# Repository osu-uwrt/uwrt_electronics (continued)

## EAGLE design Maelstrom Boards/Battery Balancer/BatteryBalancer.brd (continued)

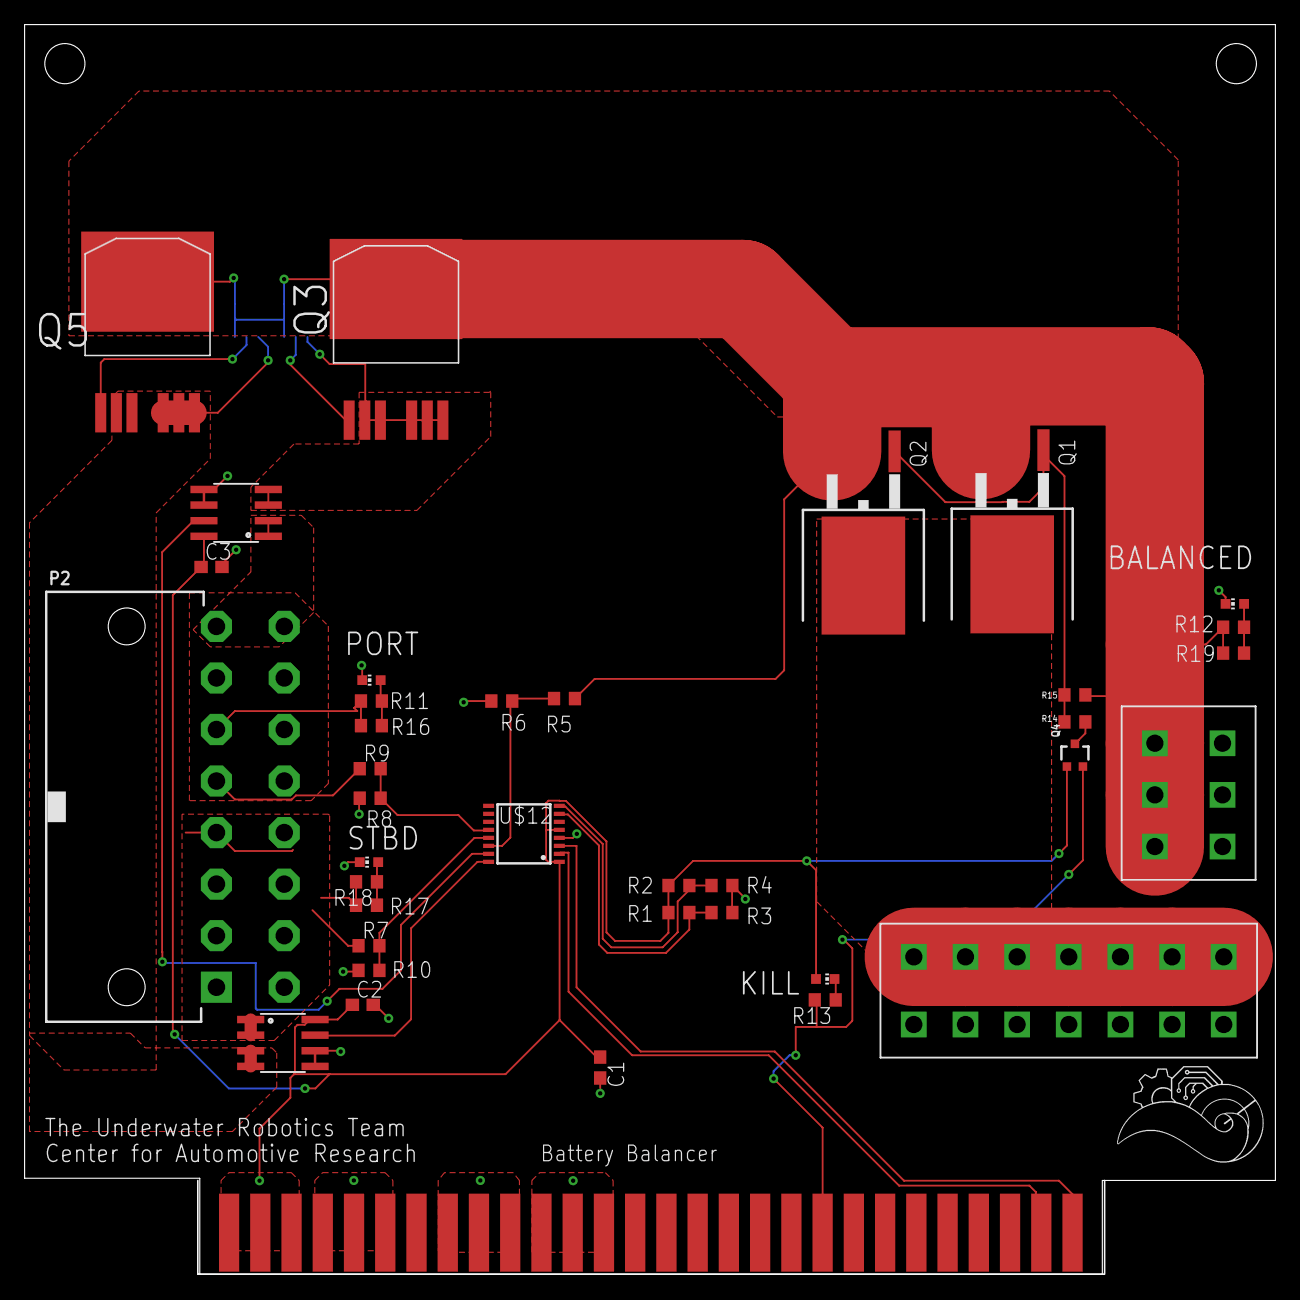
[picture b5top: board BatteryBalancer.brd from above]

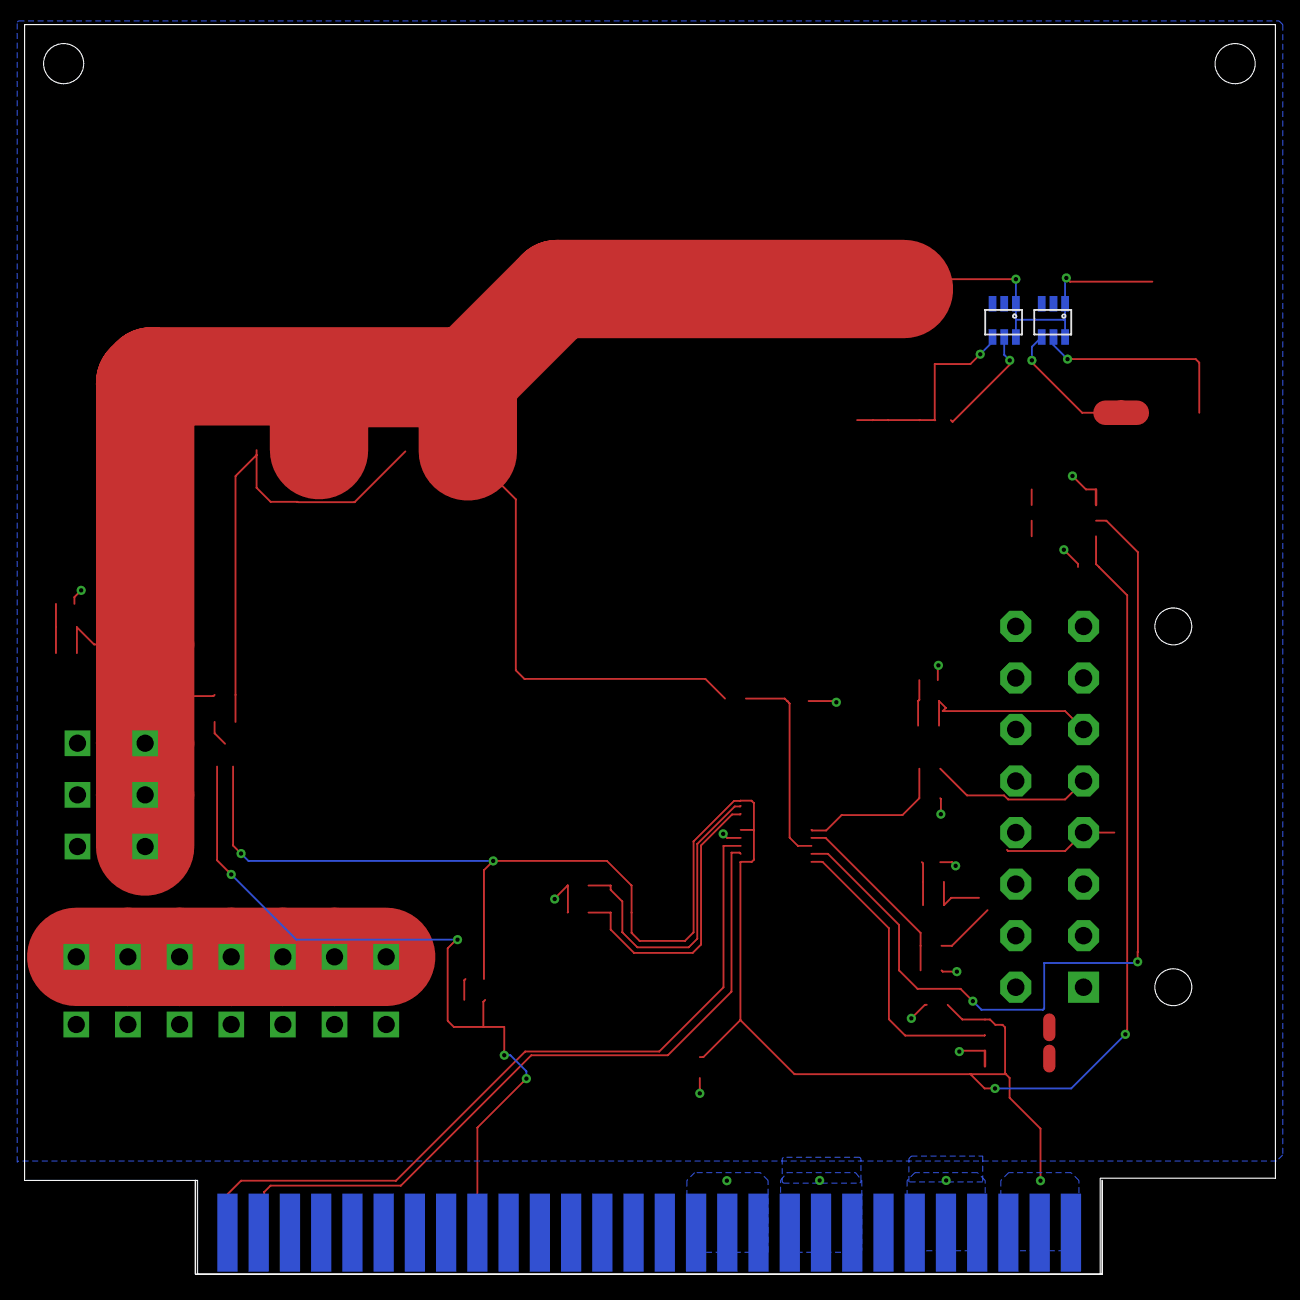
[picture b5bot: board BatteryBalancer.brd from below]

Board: 2 copper layers, 101.7 x 101.6 mm, 40 parts (2 on the bottom side), 27 nets.

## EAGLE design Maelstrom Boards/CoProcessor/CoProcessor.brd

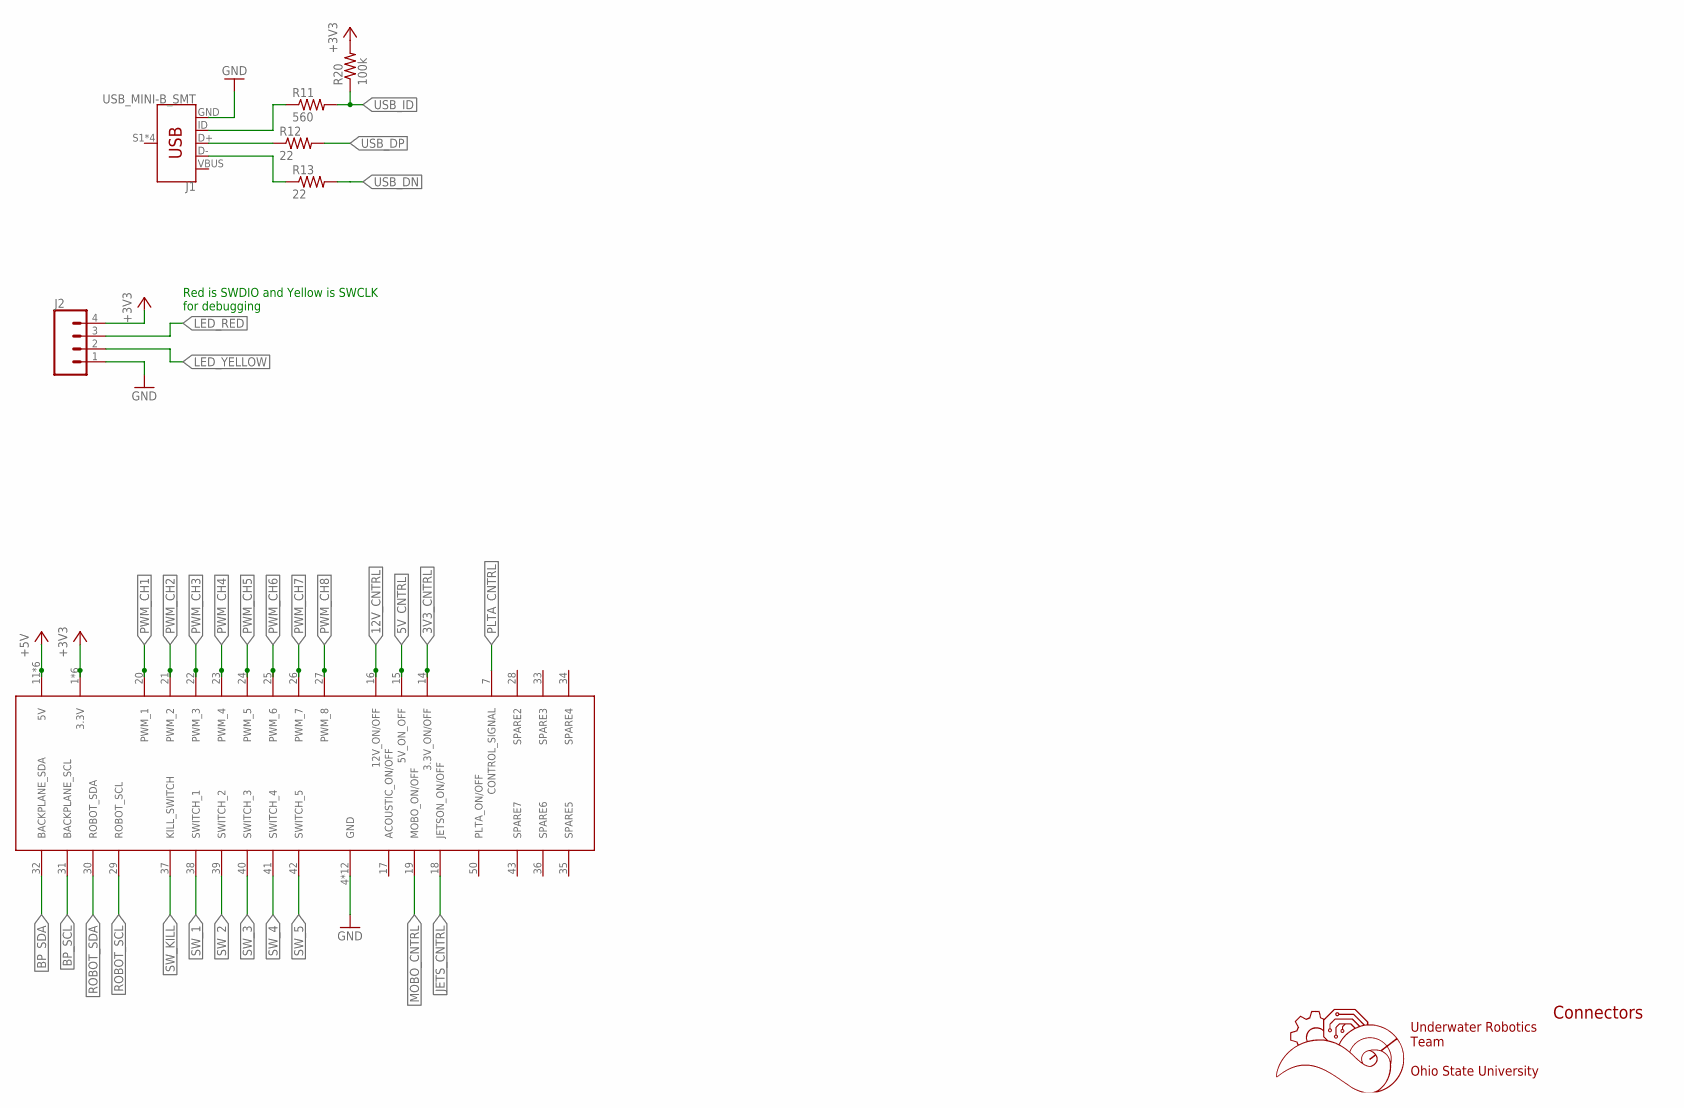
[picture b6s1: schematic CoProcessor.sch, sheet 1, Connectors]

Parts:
J1: USB_MINI-B_SMT; USB-MINIB
J2: CONN_04; 1X04
R11: 560; R0603
R12, R13: 22; R0603
R20: 100k; R0603
U$1: 5530843-EDGE; 5530843-6-BOARDFINGERS

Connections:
3V3_CNTRL: U$1.14 (3.3V_ON/OFF); also elsewhere on the board
5V_CNTRL: U$1.15 (5V_ON_OFF); also elsewhere on the board
12V_CNTRL: U$1.16 (12V_ON/OFF); also elsewhere on the board
+3V3: J2.4, R20.2, U$1.1 (3.3V), U$1.2 (3.3V), U$1.3 (3.3V), U$1.54 (3.3V), U$1.55 (3.3V), U$1.56 (3.3V); also elsewhere on the board
+5V: U$1.11 (5V), U$1.12 (5V), U$1.13 (5V), U$1.44 (5V), U$1.45 (5V), U$1.46 (5V)
BP_SCL: U$1.31 (BACKPLANE_SCL); also elsewhere on the board
BP_SDA: U$1.32 (BACKPLANE_SDA); also elsewhere on the board
GND: J1.GND, J2.1, U$1.4 (GND), U$1.5 (GND), U$1.6 (GND), U$1.8 (GND), U$1.9 (GND), U$1.10 (GND), U$1.47 (GND), U$1.48 (GND), U$1.49 (GND), U$1.51 (GND), U$1.52 (GND), U$1.53 (GND); also elsewhere on the board
JETS_CNTRL: U$1.18 (JETSON_ON/OFF); also elsewhere on the board
LED_RED: J2.3; also elsewhere on the board
LED_YELLOW: J2.2; also elsewhere on the board
MOBO_CNTRL: U$1.19 (MOBO_ON/OFF); also elsewhere on the board
unnamed: J1.ID, R11.1
unnamed: J1.D+, R12.1
unnamed: J1.D-, R13.1
PLTA_CNTRL: U$1.7 (CONTROL_SIGNAL); also elsewhere on the board
PWM_CH1: U$1.20 (PWM_1); also elsewhere on the board
PWM_CH2: U$1.21 (PWM_2); also elsewhere on the board
PWM_CH3: U$1.22 (PWM_3); also elsewhere on the board
PWM_CH4: U$1.23 (PWM_4); also elsewhere on the board
PWM_CH5: U$1.24 (PWM_5); also elsewhere on the board
PWM_CH6: U$1.25 (PWM_6); also elsewhere on the board
PWM_CH7: U$1.26 (PWM_7); also elsewhere on the board
PWM_CH8: U$1.27 (PWM_8); also elsewhere on the board
ROBOT_SCL: U$1.29 (ROBOT_SCL); also elsewhere on the board
ROBOT_SDA: U$1.30 (ROBOT_SDA); also elsewhere on the board
SW_1: U$1.38 (SWITCH_1); also elsewhere on the board
SW_2: U$1.39 (SWITCH_2); also elsewhere on the board
SW_3: U$1.40 (SWITCH_3); also elsewhere on the board
SW_4: U$1.41 (SWITCH_4); also elsewhere on the board
SW_5: U$1.42 (SWITCH_5); also elsewhere on the board
SW_KILL: U$1.37 (KILL_SWITCH); also elsewhere on the board
USB_DN: R13.2; also elsewhere on the board
USB_DP: R12.2; also elsewhere on the board
USB_ID: R11.2, R20.1
VBUS: J1.VBUS

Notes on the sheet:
Underwater Robotics Team Ohio State University
Connectors
Red is SWDIO and Yellow is SWCLK for debugging

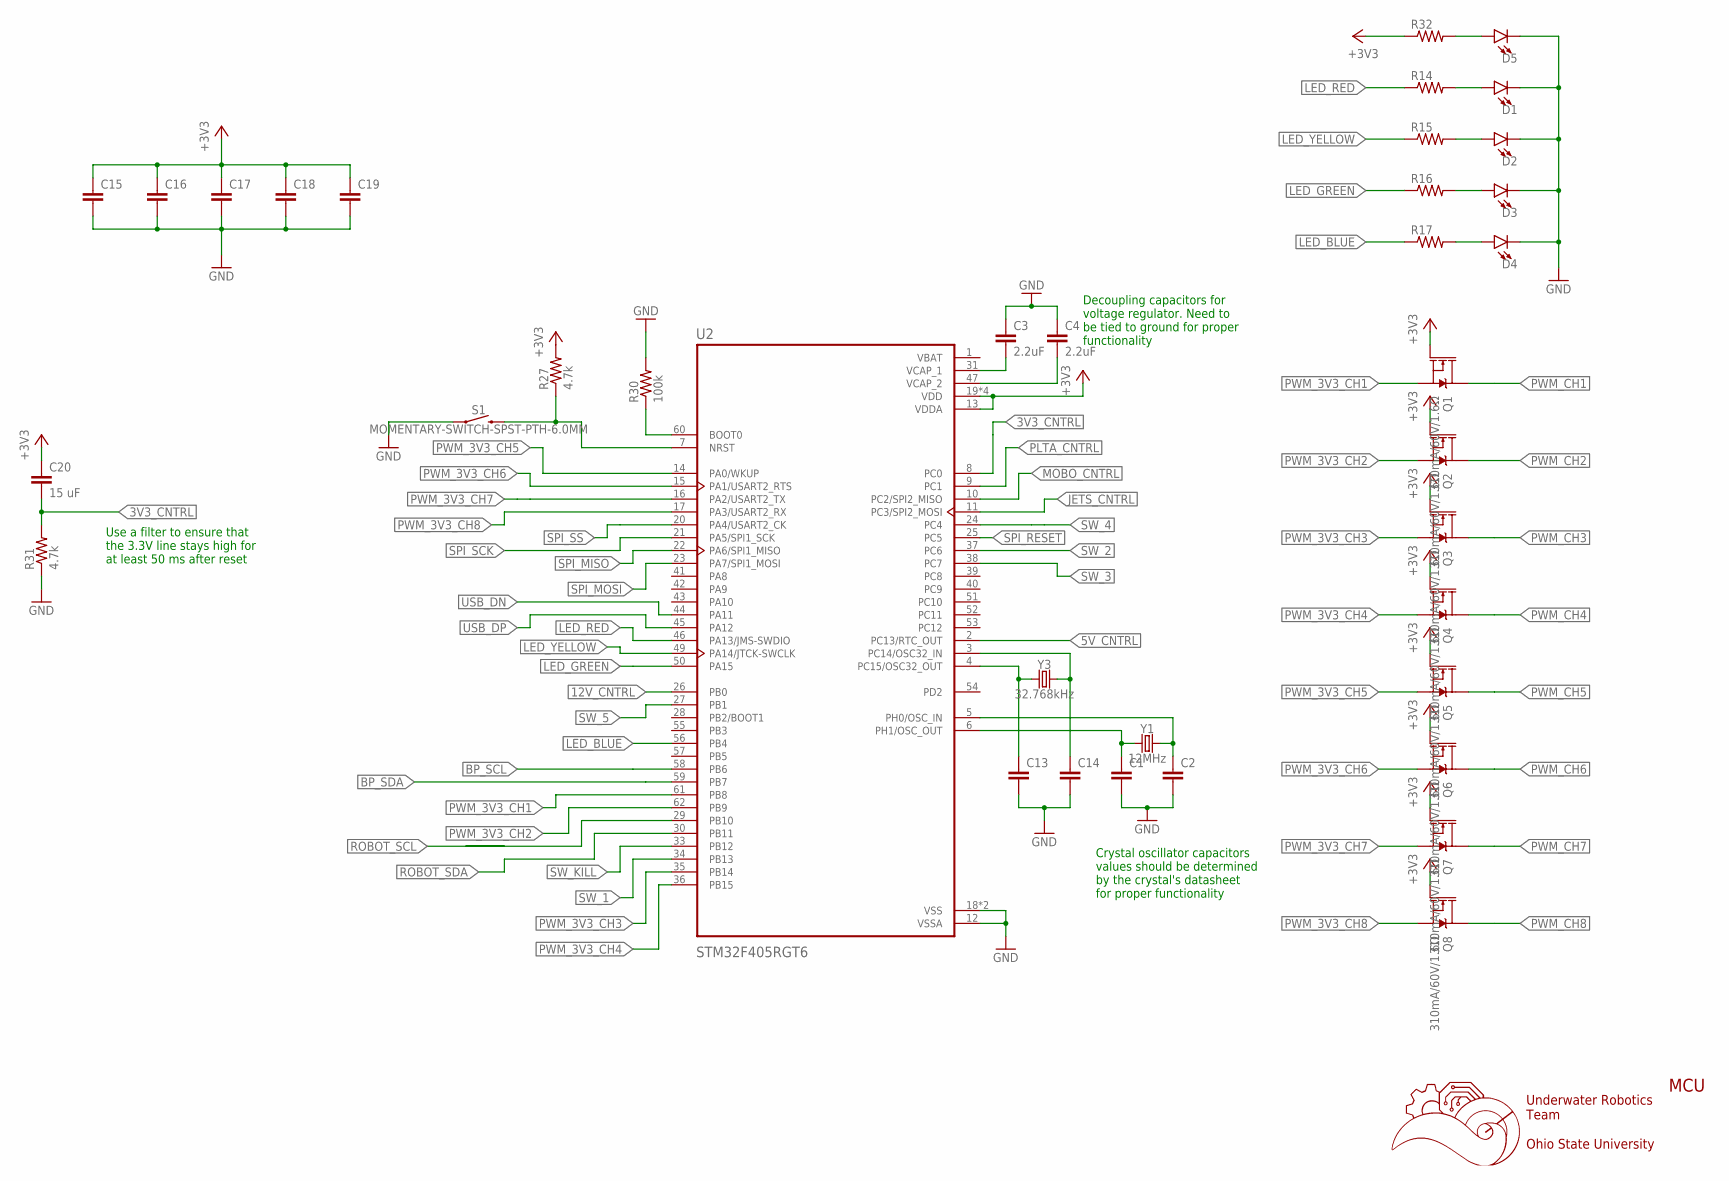
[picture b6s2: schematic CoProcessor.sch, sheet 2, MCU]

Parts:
C1, C2, C13, C14, C15, C16, C17, C18, C19: C-EUC0603; C0603
C3, C4: 2.2uF; C0603
C20: 15 uF; C050-025X075
D1, D2, D3, D4, D5: LED0603; LED-0603
Q1, Q2, Q3, Q4, Q5, Q6, Q7, Q8: 310mA/60V/1.6Ω; SOT323
R14, R15, R16, R17, R32: R-US_R0603; R0603
R27, R31: 4.7k; R0603
R30: 100k; R0603
S1: MOMENTARY-SWITCH-SPST-PTH-6.0MM; TACTILE_SWITCH_PTH_6.0MM
U2: STM32F405RGT6; QFP50P1200X1200X160-64N
Y1: 12MHz; HC49US
Y3: 32.768kHz; CRYSTAL-SMD-3.2X1.5MM

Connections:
3V3_CNTRL: C20.2, R31.2, U2.8 (PC0); also elsewhere on the board
5V_CNTRL: U2.2 (PC13/RTC_OUT); also elsewhere on the board
12V_CNTRL: U2.26 (PB0); also elsewhere on the board
+3V3: C15.1, C16.1, C17.1, C18.1, C19.1, C20.1, Q1.1 (G), Q2.1 (G), Q3.1 (G), Q4.1 (G), Q5.1 (G), Q6.1 (G), Q7.1 (G), Q8.1 (G), R27.2, R32.1, U2.13 (VDDA), U2.19 (VDD), U2.32 (VDD), U2.48 (VDD), U2.64 (VDD); also elsewhere on the board
BP_SCL: U2.58 (PB6); also elsewhere on the board
BP_SDA: U2.59 (PB7); also elsewhere on the board
GND: C1.2, C2.2, C3.1, C4.1, C13.2, C14.2, C15.2, C16.2, C17.2, C18.2, C19.2, D1.C, D2.C, D3.C, D4.C, D5.C, R30.2, R31.1, S1.1, U2.12 (VSSA), U2.18 (VSS), U2.63 (VSS); also elsewhere on the board
JETS_CNTRL: U2.11 (PC3/SPI2_MOSI); also elsewhere on the board
LED_BLUE: R17.1, U2.56 (PB4)
LED_GREEN: R16.1, U2.50 (PA15)
LED_RED: R14.1, U2.46 (PA13/JMS-SWDIO); also elsewhere on the board
LED_YELLOW: R15.1, U2.49 (PA14/JTCK-SWCLK); also elsewhere on the board
MOBO_CNTRL: U2.10 (PC2/SPI2_MISO); also elsewhere on the board
unnamed: C1.1, U2.6 (PH1/OSC_OUT), Y1.1
unnamed: D1.A, R14.2
unnamed: D2.A, R15.2
unnamed: D3.A, R16.2
unnamed: D4.A, R17.2
unnamed: C2.1, U2.5 (PH0/OSC_IN), Y1.2
unnamed: C4.2, U2.47 (VCAP_2)
unnamed: C3.2, U2.31 (VCAP_1)
unnamed: C13.1, U2.4 (PC15/OSC32_OUT), Y3.P$1 (1)
unnamed: C14.1, U2.3 (PC14/OSC32_IN), Y3.P$2 (2)
unnamed: R30.1, U2.60 (BOOT0)
unnamed: D5.A, R32.2
unnamed: R27.1, S1.3 (2), U2.7 (NRST)
PLTA_CNTRL: U2.9 (PC1); also elsewhere on the board
PWM_3V3_CH1: Q1.2 (S), U2.61 (PB8)
PWM_3V3_CH2: Q2.2 (S), U2.62 (PB9)
PWM_3V3_CH3: Q3.2 (S), U2.35 (PB14)
PWM_3V3_CH4: Q4.2 (S), U2.36 (PB15)
PWM_3V3_CH5: Q5.2 (S), U2.14 (PA0/WKUP)
PWM_3V3_CH6: Q6.2 (S), U2.15 (PA1/USART2_RTS)
PWM_3V3_CH7: Q7.2 (S), U2.16 (PA2/USART2_TX)
PWM_3V3_CH8: Q8.2 (S), U2.17 (PA3/USART2_RX)
PWM_CH1: Q1.3 (D); also elsewhere on the board
PWM_CH2: Q2.3 (D); also elsewhere on the board
PWM_CH3: Q3.3 (D); also elsewhere on the board
PWM_CH4: Q4.3 (D); also elsewhere on the board
PWM_CH5: Q5.3 (D); also elsewhere on the board
PWM_CH6: Q6.3 (D); also elsewhere on the board
PWM_CH7: Q7.3 (D); also elsewhere on the board
PWM_CH8: Q8.3 (D); also elsewhere on the board
ROBOT_SCL: U2.29 (PB10); also elsewhere on the board
ROBOT_SDA: U2.30 (PB11); also elsewhere on the board
SPI_MISO: U2.22 (PA6/SPI1_MISO); also elsewhere on the board
SPI_MOSI: U2.23 (PA7/SPI1_MOSI); also elsewhere on the board
SPI_RESET: U2.25 (PC5); also elsewhere on the board
SPI_SCK: U2.21 (PA5/SPI1_SCK); also elsewhere on the board
SPI_SS: U2.20 (PA4/USART2_CK); also elsewhere on the board
SW_1: U2.34 (PB13); also elsewhere on the board
SW_2: U2.37 (PC6); also elsewhere on the board
SW_3: U2.38 (PC7); also elsewhere on the board
SW_4: U2.24 (PC4); also elsewhere on the board
SW_5: U2.27 (PB1); also elsewhere on the board
SW_KILL: U2.33 (PB12); also elsewhere on the board
USB_DN: U2.44 (PA11); also elsewhere on the board
USB_DP: U2.45 (PA12); also elsewhere on the board
VBAT: U2.1 (VBAT)

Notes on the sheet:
Underwater Robotics Team Ohio State University
MCU
Decoupling capacitors for voltage regulator. Need to be tied to ground for proper functionality
Crystal oscillator capacitors values should be determined by the crystal's datasheet for proper functionality
Use a filter to ensure that the 3.3V line stays high for at least 50 ms after reset

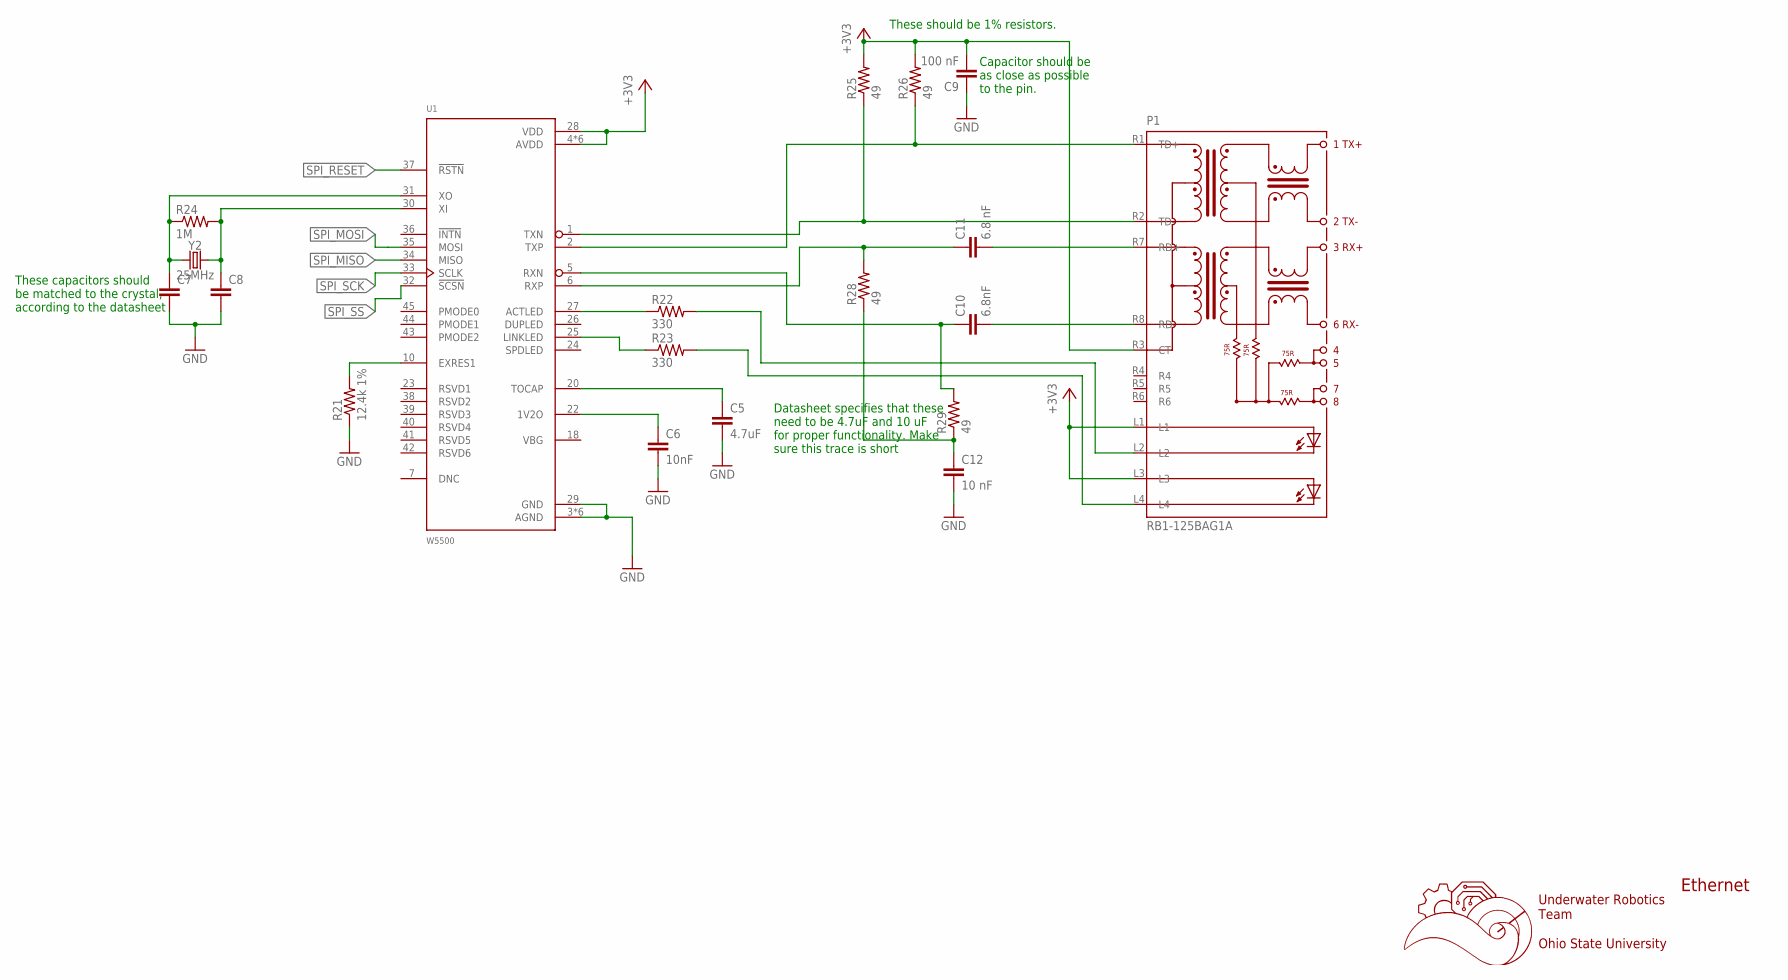
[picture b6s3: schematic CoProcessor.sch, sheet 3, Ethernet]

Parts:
C5: 4.7uF; C0603
C6: 10nF; C0603
C7, C8: C-EUC0603; C0603
C9: 100 nF; C0603
C10: 6.8nF; C0603
C11: 6.8 nF; C0603
C12: 10 nF; C0603
P1: RB1-125BAG1A; WIZNET_RB1-125BAG1A
R21: 12.4k 1%; R0603
R22, R23: 330; R0603
R24: 1M; R0603
R25, R26, R28, R29: 49; R0603
U1: W5500; QFP50P900X900X160-48N
Y2: 25MHz; HC49US

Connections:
+3V3: C9.2, P1.L1, P1.L3, P1.R3 (CT), R25.2, R26.2, U1.4 (AVDD), U1.8 (AVDD), U1.11 (AVDD), U1.15 (AVDD), U1.17 (AVDD), U1.21 (AVDD), U1.28 (VDD); also elsewhere on the board
GND: C5.2, C6.2, C7.2, C8.2, C9.1, C12.2, R21.1, U1.3 (AGND), U1.9 (AGND), U1.14 (AGND), U1.16 (AGND), U1.19 (AGND), U1.29 (GND), U1.48 (AGND); also elsewhere on the board
unnamed: C5.1, U1.20 (TOCAP)
unnamed: C6.1, U1.22 (1V2O)
unnamed: R21.2, U1.10 (EXRES1)
unnamed: P1.R2 (TD-), R25.1, U1.1 (TXN)
unnamed: P1.R1 (TD+), R26.1, U1.2 (TXP)
unnamed: C10.1, R29.2, U1.5 (RXN)
unnamed: C11.1, R28.2, U1.6 (RXP)
unnamed: P1.L2, R22.2
unnamed: P1.L4, R23.2
unnamed: R22.1, U1.27 (ACTLED)
unnamed: R23.1, U1.25 (LINKLED)
unnamed: C8.1, R24.2, U1.30 (XI), Y2.2
unnamed: C7.1, R24.1, U1.31 (XO), Y2.1
unnamed: C10.2, P1.R8 (RD-)
unnamed: C11.2, P1.R7 (RD+)
unnamed: C12.1, R28.1, R29.1
SPI_MISO: U1.34 (MISO); also elsewhere on the board
SPI_MOSI: U1.35 (MOSI); also elsewhere on the board
SPI_RESET: U1.37 (!RSTN); also elsewhere on the board
SPI_SCK: U1.33 (SCLK); also elsewhere on the board
SPI_SS: U1.32 (!SCSN); also elsewhere on the board

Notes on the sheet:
Underwater Robotics Team Ohio State University
Ethernet
Datasheet specifies that these need to be 4.7uF and 10 uF for proper functionality. Make sure this trace is short
These capacitors should be matched to the crystal, according to the datasheet
These should be 1% resistors.
Capacitor should be as close as possible to the pin.

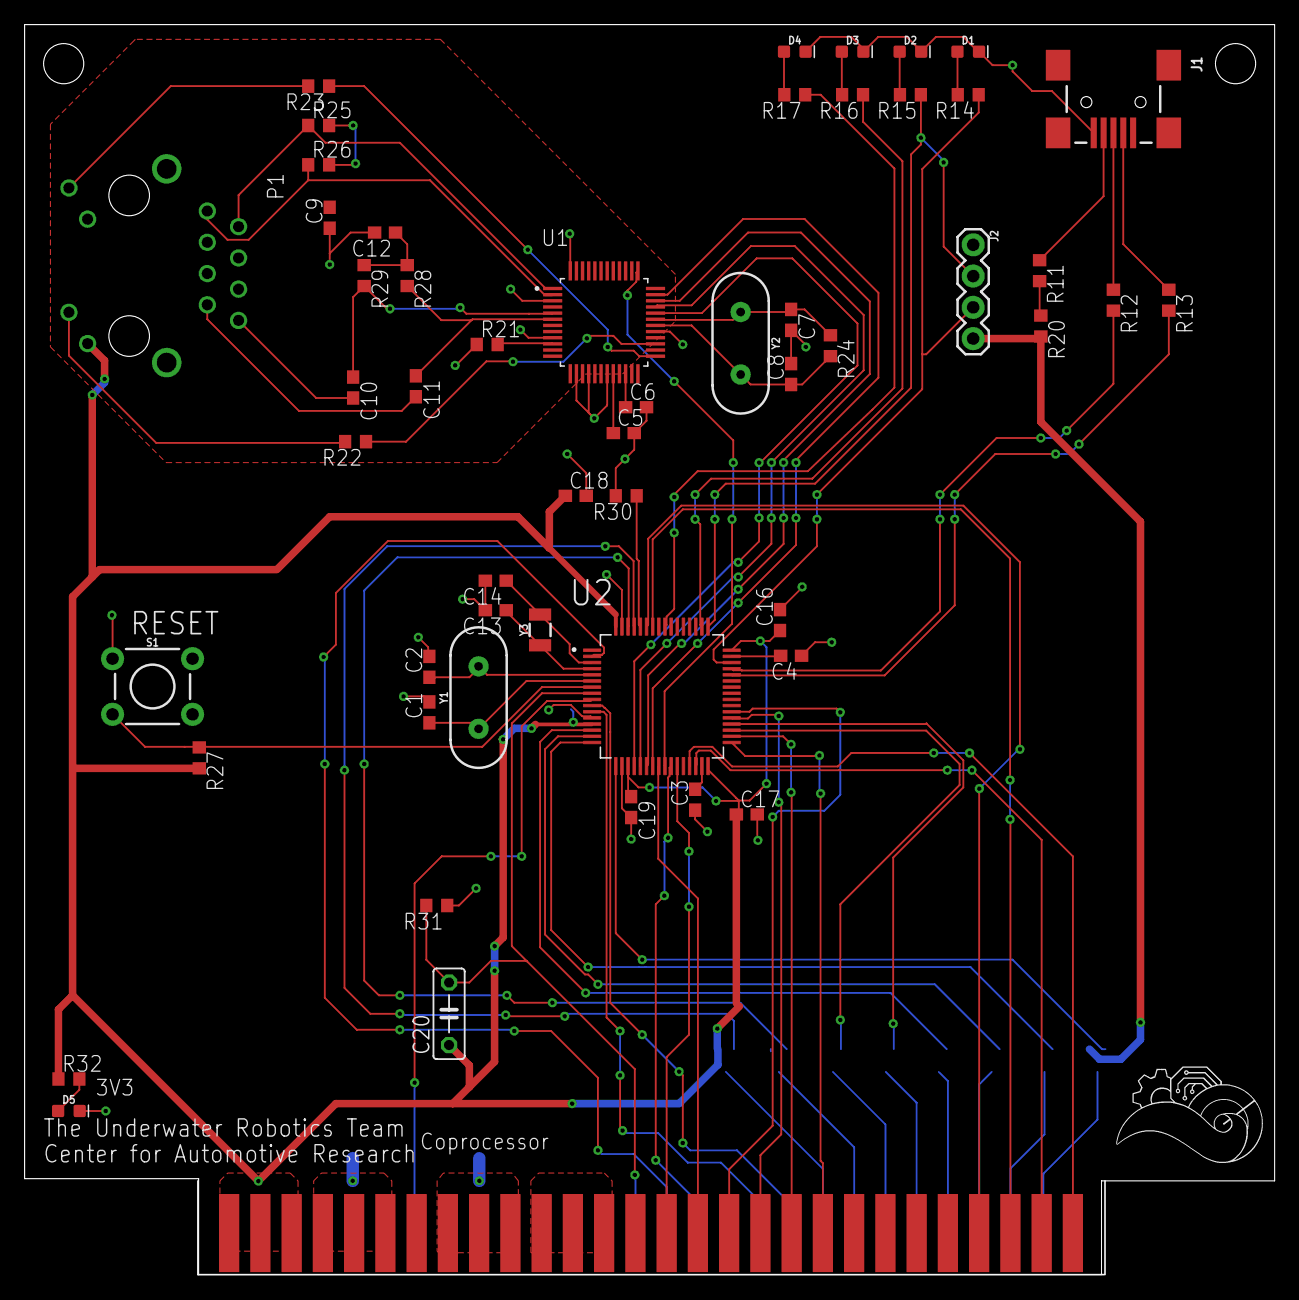
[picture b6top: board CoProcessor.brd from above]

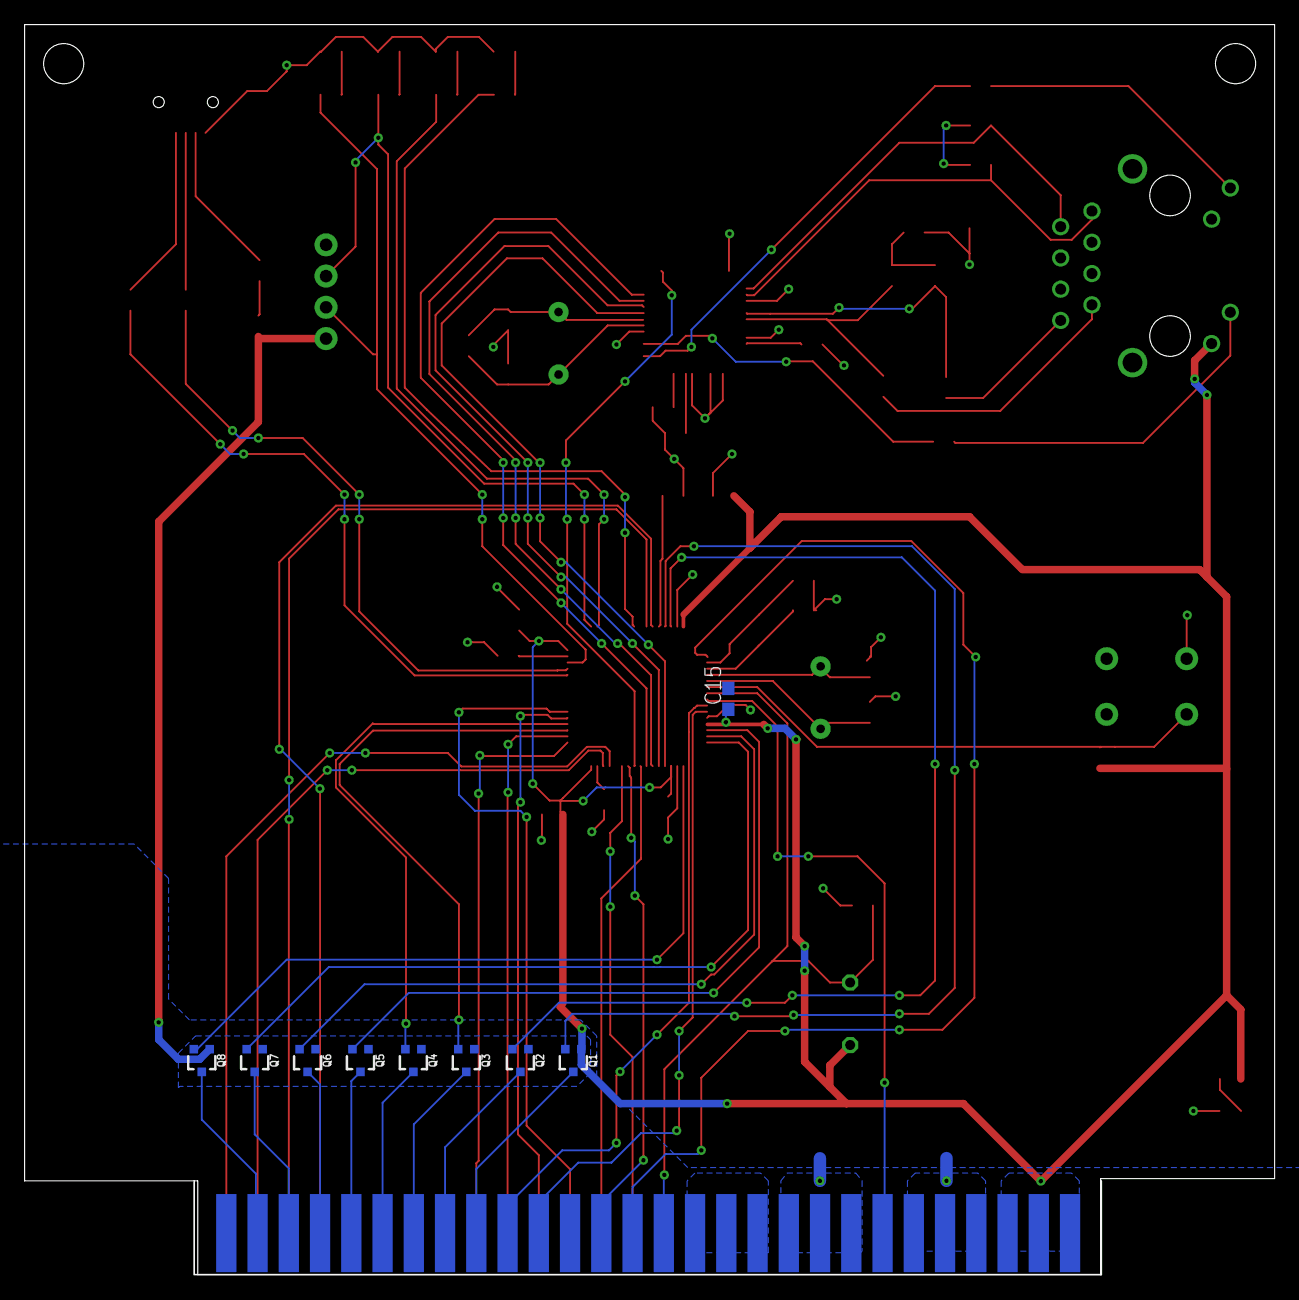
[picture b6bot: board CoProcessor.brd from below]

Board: 2 copper layers, 101.6 x 101.6 mm, 63 parts (9 on the bottom side), 79 nets.
